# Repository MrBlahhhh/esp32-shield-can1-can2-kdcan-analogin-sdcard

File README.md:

# ESP32-S3 automotive I/O carrier — two CAN buses, K-line, microSD, analog

## TL;DR

A carrier board an **ESP32-S3-DevKitC-1 plugs into**, turning it into a
vehicle data logger. The dev board brings the MCU and its power; this board
brings everything that has to touch a car.

- **Two CAN buses at once.** One on the ESP32's own TWAI controller, one on
  an MCP2518FD over SPI — because the S3 has exactly one TWAI and two
  transceivers on it would only ever give you a choice, not both.
- **K-line (ISO 9141 / KWP2000) as well**, so a BMW/MINI K+DCAN cable is
  covered end to end. A solder jumper picks whether the aux harness pins
  carry K-line or the second CAN pair; the two cannot share a wire.
- **Four analog channels, read differentially.** The sensor loom's own
  ground comes back as a Kelvin wire through an attenuator matched to the
  signal channels', so chassis offset subtracts out exactly instead of
  landing on every reading.
- **The card survives ignition-off.** A supercapacitor bank holds the 5 V
  rail for about 825 ms after the supply goes away — six times what the board
  this forked from shipped with, and long enough to finish the block in
  flight and close the file.
- **The Python in `gen/` is the source.** It generates, places, routes,
  audits and circuit-simulates the whole board; the KiCad files are build
  outputs. `python gen/build_board.py` rebuilds the PCB from nothing.
- **The firmware runs before the board exists.** `gen/simulate_firmware.py`
  compiles the real sketch for the PC against a model of this board and
  feeds it CAN frames, sensor voltages and a power cut.
- **State: routed clean, simulated, firmware ported, never manufactured.**

## Why a carrier and not a shield

It was going to be a shield. It measured out at 1.4× the dev board's entire
area before a single track was drawn, so it isn't one — the DevKitC-1 drops
into two 22-way sockets on a board considerably larger than itself.

Worth being plain: at **98 × 100 mm** this is no smaller than the standalone
board it forked from. What it buys is a replaceable MCU with no module to
reflow, and a second CAN bus and a K-line the parent never had.

| | |
|---|---|
| Board | 98 × 100 mm, 4 layer |
| Parts | 153 component instances, 70 distinct BOM lines |
| Nets | 90 |
| Assembly | 128 surface-mount designators across 48 fab BOM lines |

## What's on it

| Block | Detail |
|---|---|
| **CAN 1** | TJA1051T/3 on the ESP32's TWAI. Common-mode choke, split termination (off by default), bidirectional clamps. |
| **CAN 2** | MCP2518FD (SOIC-14) on SPI with a 40 MHz crystal, its own TJA1051, choke, termination and clamps. |
| **K-line** | Discrete: 2N7002 low-side driver, clamped 22k/10k receiver, optional ISO 9141 tester pull-up on a jumper. |
| **Analog** | 4 channels, fixed 0–16 V divider (0.1 % where it sets the gain, 0.235 % worst case, no calibration needed), pull-up jumper per channel, two ADS1115s, shared Kelvin ground return. |
| **microSD** | 1-bit SDMMC, switched card supply, ESD arrays on every contact. |
| **Hold-up** | 2 × 0.33 F 2.7 V supercaps in series on the 5 V rail, TLV431 power-fail detector tripping at 4.20 V. |
| **Shift light** | 74AHCT1G125 buffer so WS2812 DIN is a real 5 V, fused tap, 3-pin header. |

There is **no power conversion**. Both rails come up from the dev board's
sockets — 5 V from its USB-C behind its own Schottky, 3.3 V from its LDO.
The only 12 V the board sees is OBD-II pin 16, and that is sense-only.

## Pin map

All 24 usable DevKitC-1 GPIOs are allocated; nothing is spare. Pins are
grouped by which socket row they are on, because each row is 22 through-holes
that cut a 53 mm slot through every inner layer — a signal crossing one has
no return path underneath it.

| J1 row (left of the board) | | J3 row (right) | |
|---|---|---|---|
| IO4–IO7 | AIN1–4 | IO1, IO2 | K-line RX / TX |
| IO8 | battery sense | IO39–IO42 | CAN 2 SPI (SCK/MOSI/MISO/CS) |
| IO9, IO10 | I²C SCL / SDA | IO21 | CAN 2 interrupt |
| IO11 | SD card detect | IO47 | SD supply enable |
| IO12–IO14 | SD D0 / CMD / CLK | IO48 | WS2812 data |
| IO15 | power fail | | |
| IO16–IO18 | CAN 1 S / TX / RX | | |

Exactly one net crosses sides — `SD_PWR_EN`, a load-switch gate — and it
routes around the end of the row rather than through it.

The analog channels must live in IO1–IO10 because ADC2 is unusable with the
radio up. After the SD bus takes IO9–IO14 and IO3 is excluded as a strapping
pin, IO4–IO8 are exactly the five that remain.

## Ordering

```
python gen/export_fab.py      # gerbers, positions, JLC BOM
python gen/export_order.py    # LCSC shopping list + what to buy elsewhere
```

Every one of the 48 fab BOM lines carries an LCSC part number, and each was
checked against the live catalogue rather than assumed — see
[`docs/PARTS.md`](docs/PARTS.md) for what that turned up, including three
part numbers that were confidently wrong and two footprints that would not
have soldered. [`docs/COST.md`](docs/COST.md) prices the result and identifies
about $5.70 a board of savings that cost nothing functional.

`fab/order-elsewhere.csv` lists what LCSC's assembly flow cannot supply:
the through-hole connectors, the two supercapacitors and the dev board.

**The order is ready and paused.** Everything is verified — gerbers, BOM,
placements, both JLCPCB quotes and an LCSC cart — and it is on hold because
US customs adds 35% of merchandise value. See
[`docs/TODO.md`](docs/TODO.md) for the state of play and the resume
checklist, and [`docs/COST.md`](docs/COST.md) for the quotes and the
hand-build-versus-assembled comparison.

## Verification

| | |
|---|---|
| `gen/validate.py` | schematic re-extracted through KiCad and compared net for net; ERC clean |
| `gen/build_board.py` | places, routes, and runs DRC — **0 violations, 0 unconnected** |
| `gen/simulate_firmware.py` | **50 checks**, the real sketch compiled for the host against a model of this board |
| `gen/mutate_firmware.py` | deliberately breaks the firmware 17 ways to prove the suite notices — **17 of 17 caught** |
| `gen/simulate.py` | ngspice: analog channel, crank, CAN bus, system budgets, log fidelity |
| `gen/audit_*.py` | docs, polarity, straps, paste, mechanical, PCB, routes, schematic readability |

Study 0 of the firmware suite is the one everything else rests on: it dumps
the simulator's pin map and compares it to `netlist.txt`, so a model built
from prose instead of the design fails loudly rather than validating the
wrong board.

## Wanted, not yet built

[`docs/TODO.md`](docs/TODO.md) — additions nobody has started, as opposed to
the defects below, plus the state of the paused parts order. Currently two
sensor additions, and **neither needs a board change**:

- **Exhaust gas temperature** through an MCP9600 on the I2C header. Entirely
  firmware.
- **Wideband AFR** from a DIY-EFI TinyWB. Its 0–5 V output drops straight
  into a sensor channel with nothing to change at all — that is the input
  the analogue front end was designed around. The open question is its
  10–20 AFR scaling, which clips anything richer than 10.0.

## Known open

- ~~**`ROW_PITCH` is an assumption.**~~ **Settled — 22.86 mm is correct**, from
  Espressif's own DXF. The pad columns sit at x = 1.270 and x = 24.130, 22
  pads each over y 7.960–61.300 (53.34 mm = 21 × 2.54), so the spacing is
  24.130 − 1.270 = **22.860 mm exactly**. It closes against the board width
  too: 1.270 + 22.860 + 1.270 = 25.400.

  Worth knowing that a figure of "25.4 mm row spacing on a 27.9 mm board"
  circulates for this part. That is the **original ESP32-DevKitC** with the
  WROOM-32 module, which really is wider. On the S3, 25.40 mm is the board
  width — the tell is that a 25.5 mm body with 25.4 mm rows would put the pin
  centres 0.05 mm from the edge.
- **No antenna keepout.** The module is on the dev board now, radiating from
  about 8.5 mm above this laminate. Copper underneath still detunes it, but
  which end of the outline to clear needs measuring off the same DXF.
- **The hold-up timings are calculated, not measured.** 825 ms shed /
  254 ms unshed come from `t = C·dV/I`; the ngspice study for the supercap
  bank has not been written, and ESR and the Schottky's drop over
  temperature will both eat into them.
- **Check the dev board revision.** v1.1 puts the onboard RGB LED on IO38,
  which this board leaves free for it. Some revisions use IO48, which is the
  WS2812 output here and would clash.
- **The schematic still has about 20 text collisions** out of the ~150 it
  started with, mostly a label brushing a neighbour inside a hand-drawn
  block. `gen/audit_schematic.py` lists each one with coordinates.
- **Two bypass capacitors sit 8.7 mm from the pin they bypass**, against the
  6 mm `gen/audit_pcb.py` asks for. That is the width of the SOIC-8 itself:
  the shelf packer keeps each bypass immediately beside its IC, but fills
  left to right, so the capacitor lands on the opposite side of the package
  from the supply pin. Down from 42 mm, and fine for 500 kbit/s CAN with
  22 µF of bulk on the same rail, but it is the one placement the audit
  still objects to.

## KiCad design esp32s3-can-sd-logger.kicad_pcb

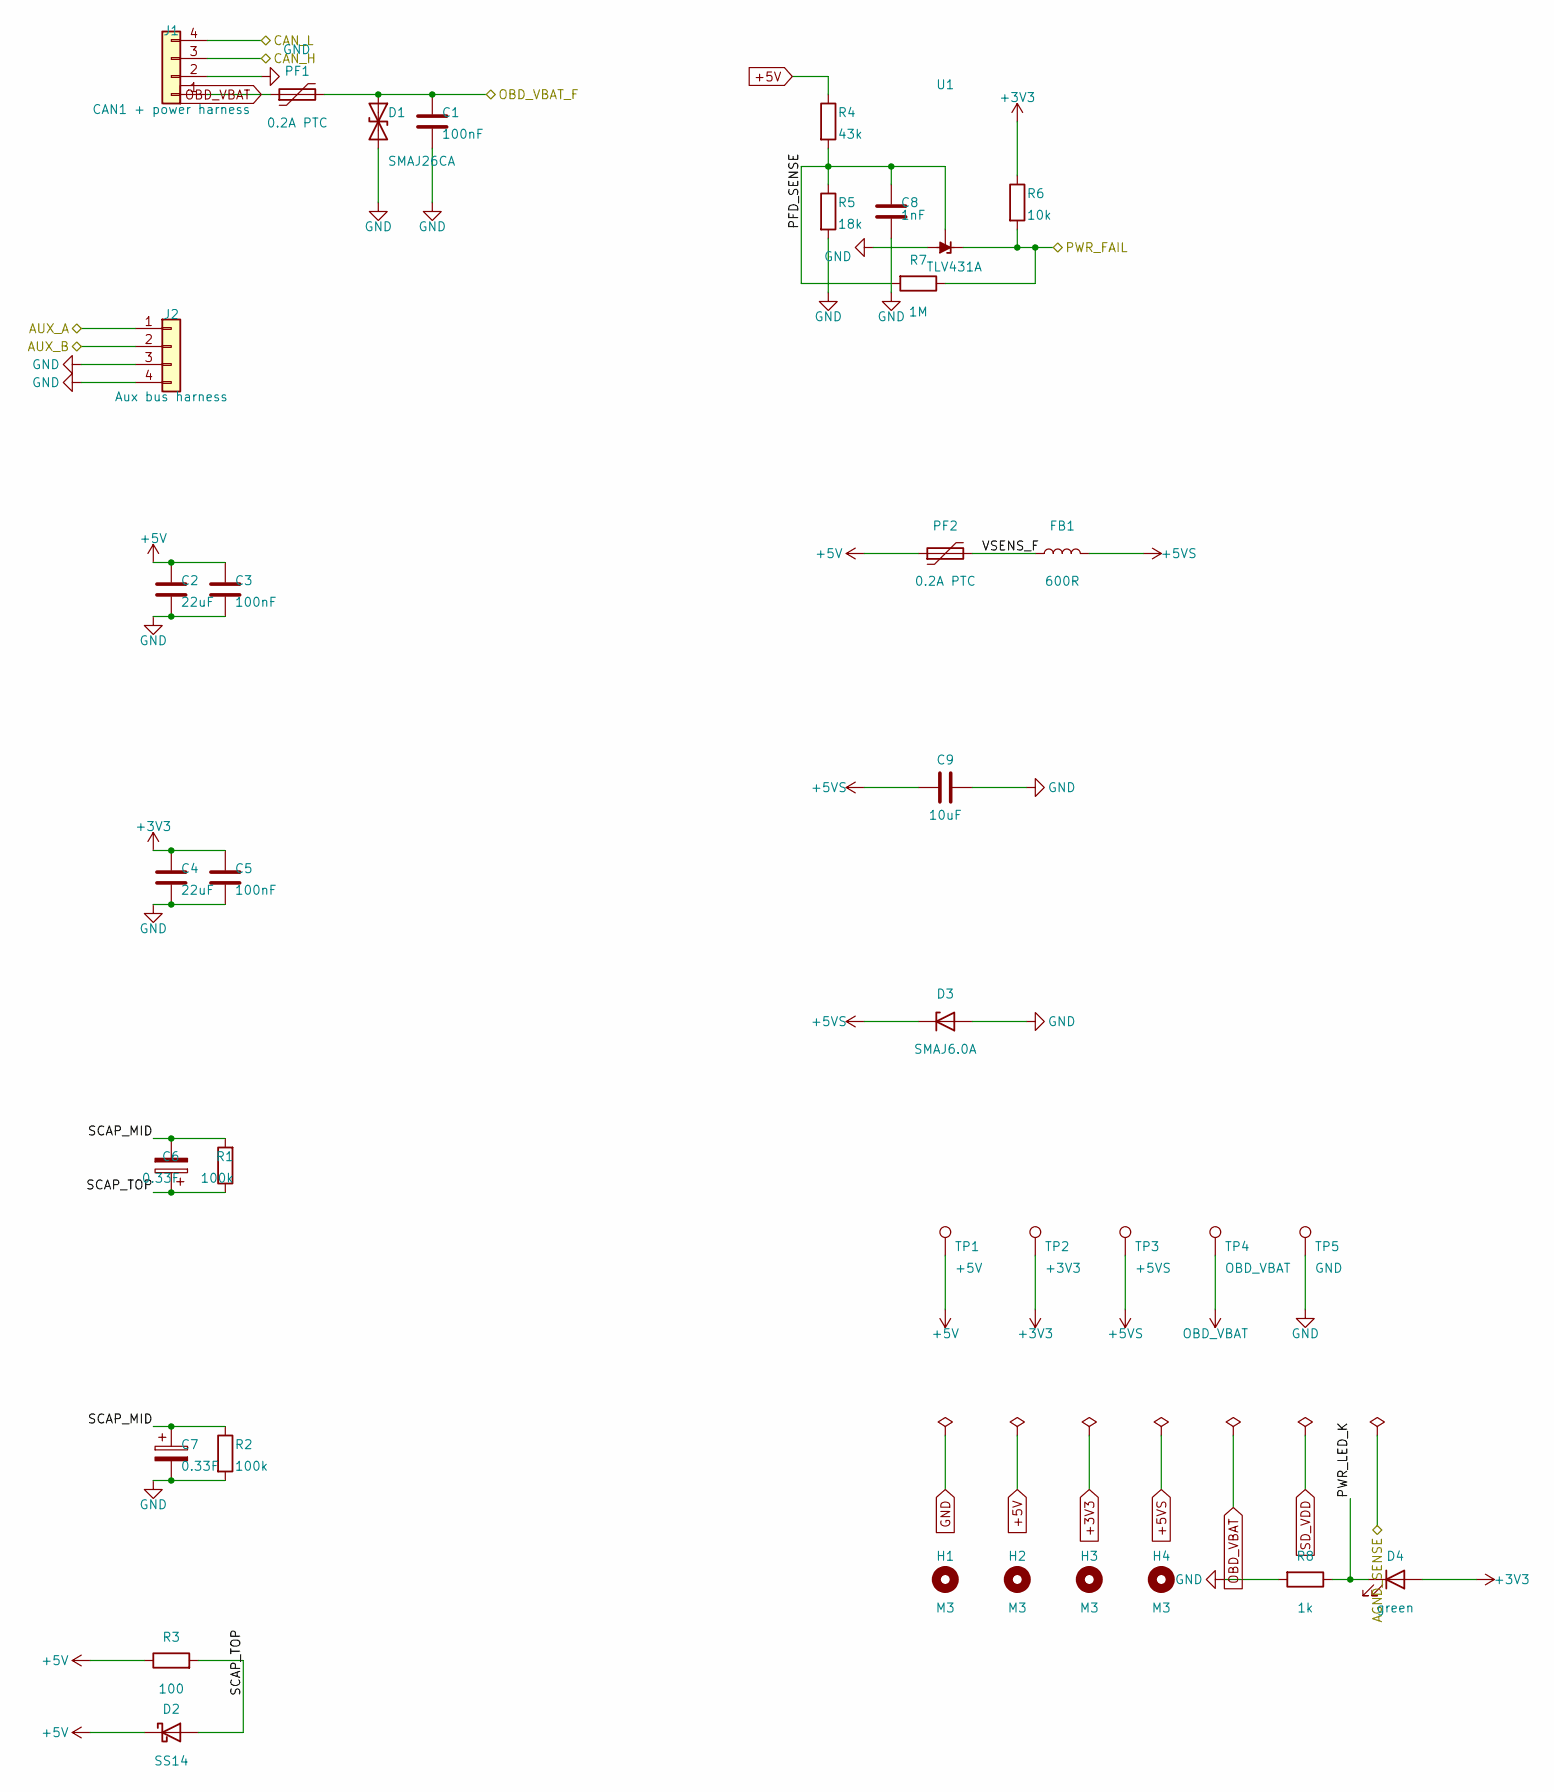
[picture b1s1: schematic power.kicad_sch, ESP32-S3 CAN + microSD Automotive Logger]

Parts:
C1: 100nF; C_0805_2012Metric; Voltage 100V
C2, C4: 22uF; C_1206_3216Metric; Voltage 16V
C3, C5: 100nF; C_0805_2012Metric; Voltage 16V
C6, C7: 0.33F; CP_Radial_D8.0mm_P3.50mm; Voltage 2.7V; MPN Eaton HB1030-2R5105-R
C8: 1nF; C_0805_2012Metric; Voltage 50V
C9: 10uF; C_1206_3216Metric; Voltage 16V
D1: SMAJ26CA; D_SMA; MPN Diodes Inc SMAJ26CA-13-F
D2: SS14; D_SMA; MPN SS14
D3: SMAJ6.0A; D_SMA; MPN Littelfuse SMAJ6.0A
D4: green; LED_0805_2012Metric
FB1: 600R; L_0805_2012Metric; MPN Wurth 742792022
H1, H2, H3, H4: M3; MountingHole_3.2mm_M3
J1: CAN1 + power harness; JST_PH_B4B-PH-K_1x04_P2.00mm_Vertical; MPN JST B4B-PH-K-S(LF)(SN)
J2: Aux bus harness; JST_PH_B4B-PH-K_1x04_P2.00mm_Vertical; MPN JST B4B-PH-K-S(LF)(SN)
PF1, PF2: 0.2A PTC; R_1812_4532Metric; MPN Bourns MF-MSMF020/60-2
R1, R2: 100k; R_0805_2012Metric
R3: 100; R_1206_3216Metric
R4: 43k; R_0805_2012Metric; Tolerance 1%
R5: 18k; R_0805_2012Metric; Tolerance 1%
R6: 10k; R_0805_2012Metric
R7: 1M; R_0805_2012Metric
R8: 1k; R_0805_2012Metric
TP1: +5V; TestPoint_Pad_D1.5mm
TP2: +3V3; TestPoint_Pad_D1.5mm
TP3: +5VS; TestPoint_Pad_D1.5mm
TP4: OBD_VBAT; TestPoint_Pad_D1.5mm
TP5: GND; TestPoint_Pad_D1.5mm
U1: TLV431A; SOT-23; MPN TLV431ASN1T1G

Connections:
+3V3: C4.1, C5.1, D4.2 (A), R6.1, TP2.1; also elsewhere on the board
+5V: C2.1, C3.1, D2.1 (K), PF2.1, R3.1, R4.1, TP1.1; also elsewhere on the board
+5VS: C9.1, D3.1 (K), FB1.2, TP3.1; also elsewhere on the board
AUX_A: J2.1; also elsewhere on the board
AUX_B: J2.2; also elsewhere on the board
CAN_H: J1.3; also elsewhere on the board
OBD_VBAT: J1.1, PF1.1, TP4.1; also elsewhere on the board
OBD_VBAT_F: C1.1, D1.1 (A1), PF1.2; also elsewhere on the board
PFD_SENSE: C8.1, R4.2, R5.1, R7.2, U1.2 (REF)
PWR_FAIL: R6.2, R7.1, U1.1 (K); also elsewhere on the board
PWR_LED_K: D4.1 (K), R8.1
SCAP_MID: C6.2, C7.1, R1.2, R2.1
SCAP_TOP: C6.1, D2.2 (A), R1.1, R3.2
VSENS_F: FB1.1, PF2.2

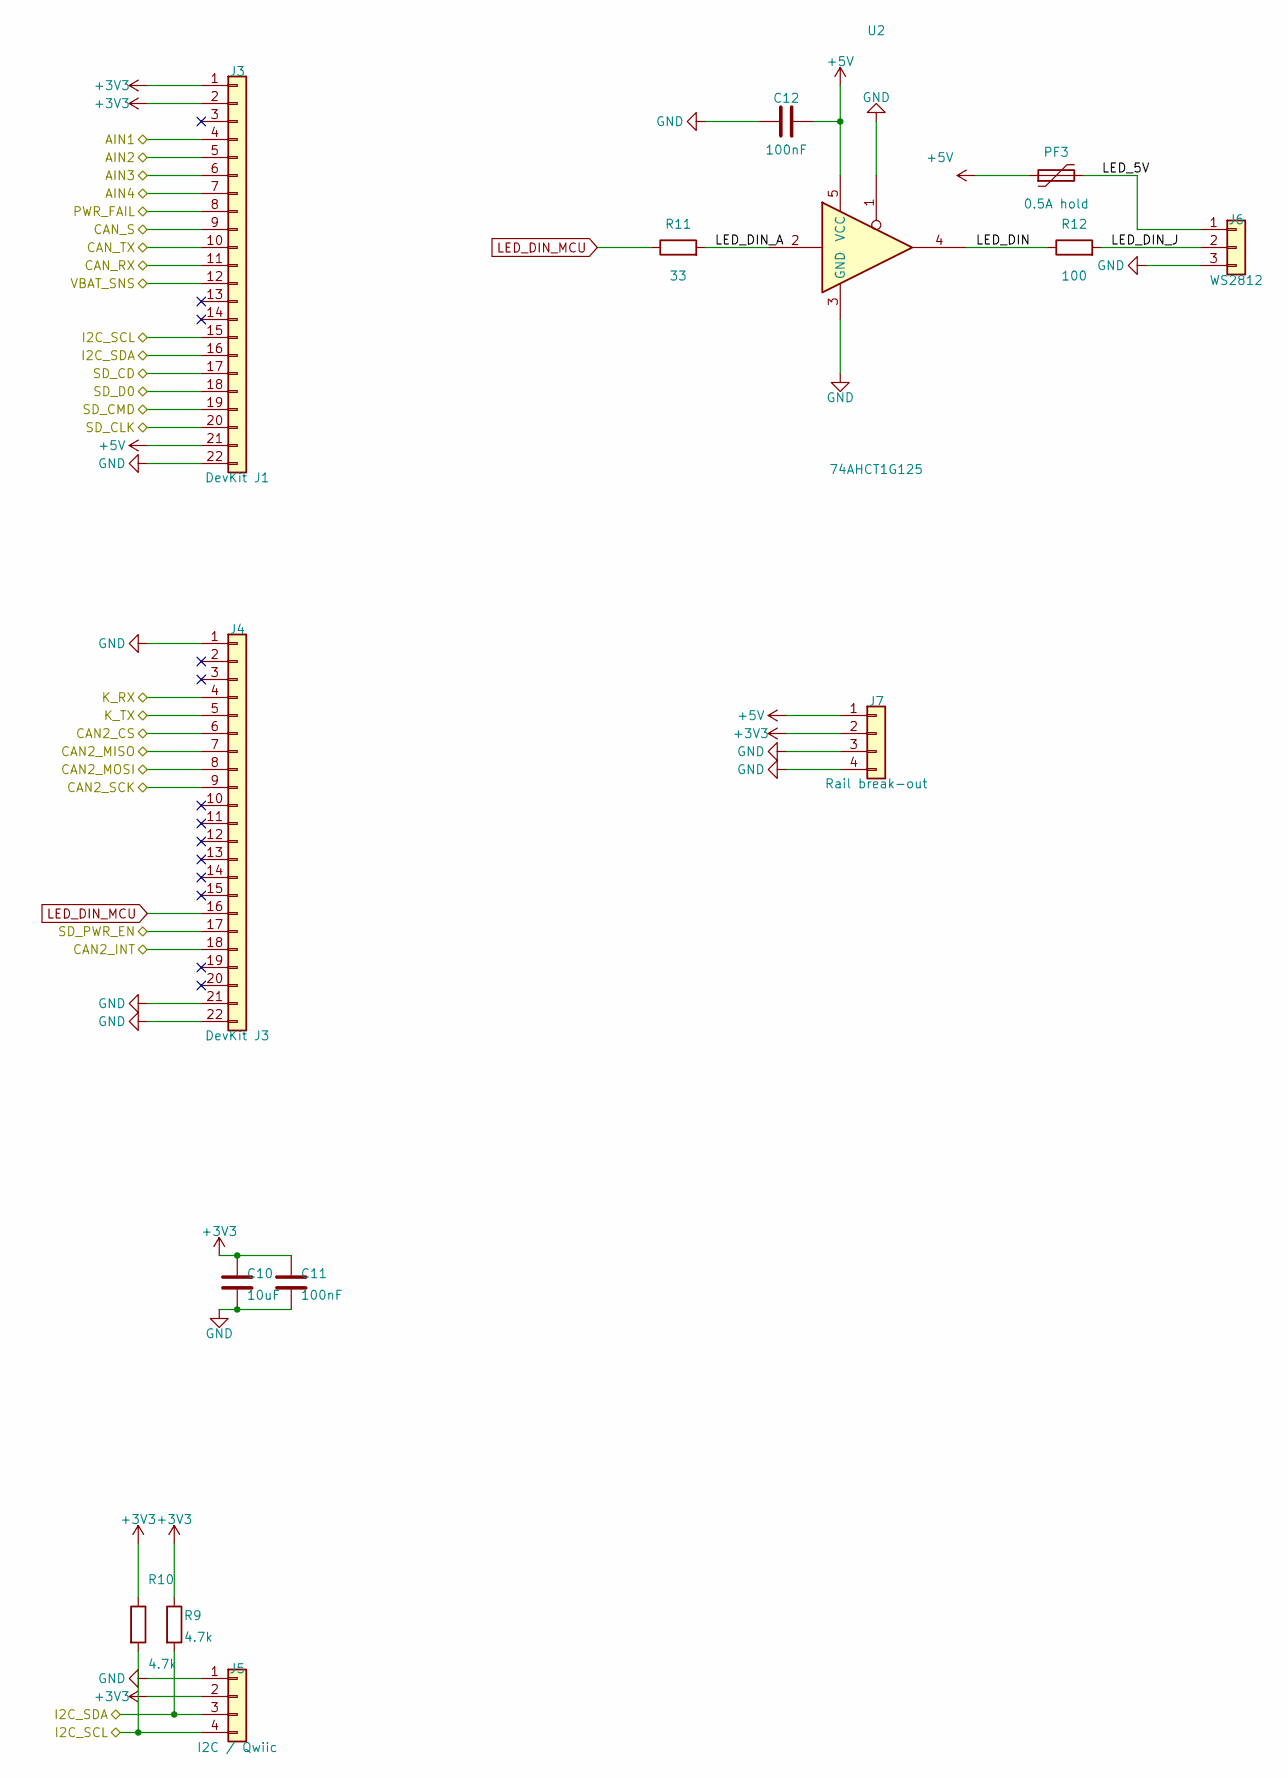
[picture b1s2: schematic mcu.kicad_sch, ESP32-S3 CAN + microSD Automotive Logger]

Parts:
C10: 10uF; C_1206_3216Metric; Voltage 16V
C11, C12: 100nF; C_0805_2012Metric; Voltage 16V
J3: DevKit J1; PinSocket_1x22_P2.54mm_Vertical; MPN ESP32-S3-DevKitC-1 J1
J4: DevKit J3; PinSocket_1x22_P2.54mm_Vertical; MPN ESP32-S3-DevKitC-1 J3
J5: I2C / Qwiic; PinHeader_1x04_P2.54mm_Vertical
J6: WS2812; PinHeader_1x03_P2.54mm_Vertical
J7: Rail break-out; PinHeader_1x04_P2.54mm_Vertical
PF3: 0.5A hold; R_1812_4532Metric; MPN Bourns MF-MSMF050-2
R9, R10: 4.7k; R_0805_2012Metric
R11: 33; R_0805_2012Metric
R12: 100; R_0805_2012Metric
U2: 74AHCT1G125; SOT-23-5; MPN SN74AHCT1G125DBVR

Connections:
+3V3: C10.1, C11.1, J3.1, J3.2, J5.2, J7.2, R9.1, R10.1; also elsewhere on the board
+5V: C12.1, J3.21, J7.1, PF3.1, U2.5 (VCC); also elsewhere on the board
AIN1: J3.4; also elsewhere on the board
AIN2: J3.5; also elsewhere on the board
AIN3: J3.6; also elsewhere on the board
AIN4: J3.7; also elsewhere on the board
CAN2_CS: J4.6; also elsewhere on the board
CAN2_INT: J4.18; also elsewhere on the board
CAN2_MISO: J4.7; also elsewhere on the board
CAN2_MOSI: J4.8; also elsewhere on the board
CAN2_SCK: J4.9; also elsewhere on the board
CAN_RX: J3.11; also elsewhere on the board
CAN_S: J3.9; also elsewhere on the board
CAN_TX: J3.10; also elsewhere on the board
I2C_SCL: J3.15, J5.4, R10.2; also elsewhere on the board
I2C_SDA: J3.16, J5.3, R9.2; also elsewhere on the board
K_RX: J4.4; also elsewhere on the board
K_TX: J4.5; also elsewhere on the board
LED_5V: J6.1, PF3.2
LED_DIN: R12.1, U2.4
LED_DIN_A: R11.2, U2.2
LED_DIN_J: J6.2, R12.2
LED_DIN_MCU: J4.16, R11.1
PWR_FAIL: J3.8; also elsewhere on the board
SD_CD: J3.17; also elsewhere on the board
SD_CLK: J3.20; also elsewhere on the board
SD_CMD: J3.19; also elsewhere on the board
SD_D0: J3.18; also elsewhere on the board
SD_PWR_EN: J4.17; also elsewhere on the board
VBAT_SNS: J3.12; also elsewhere on the board

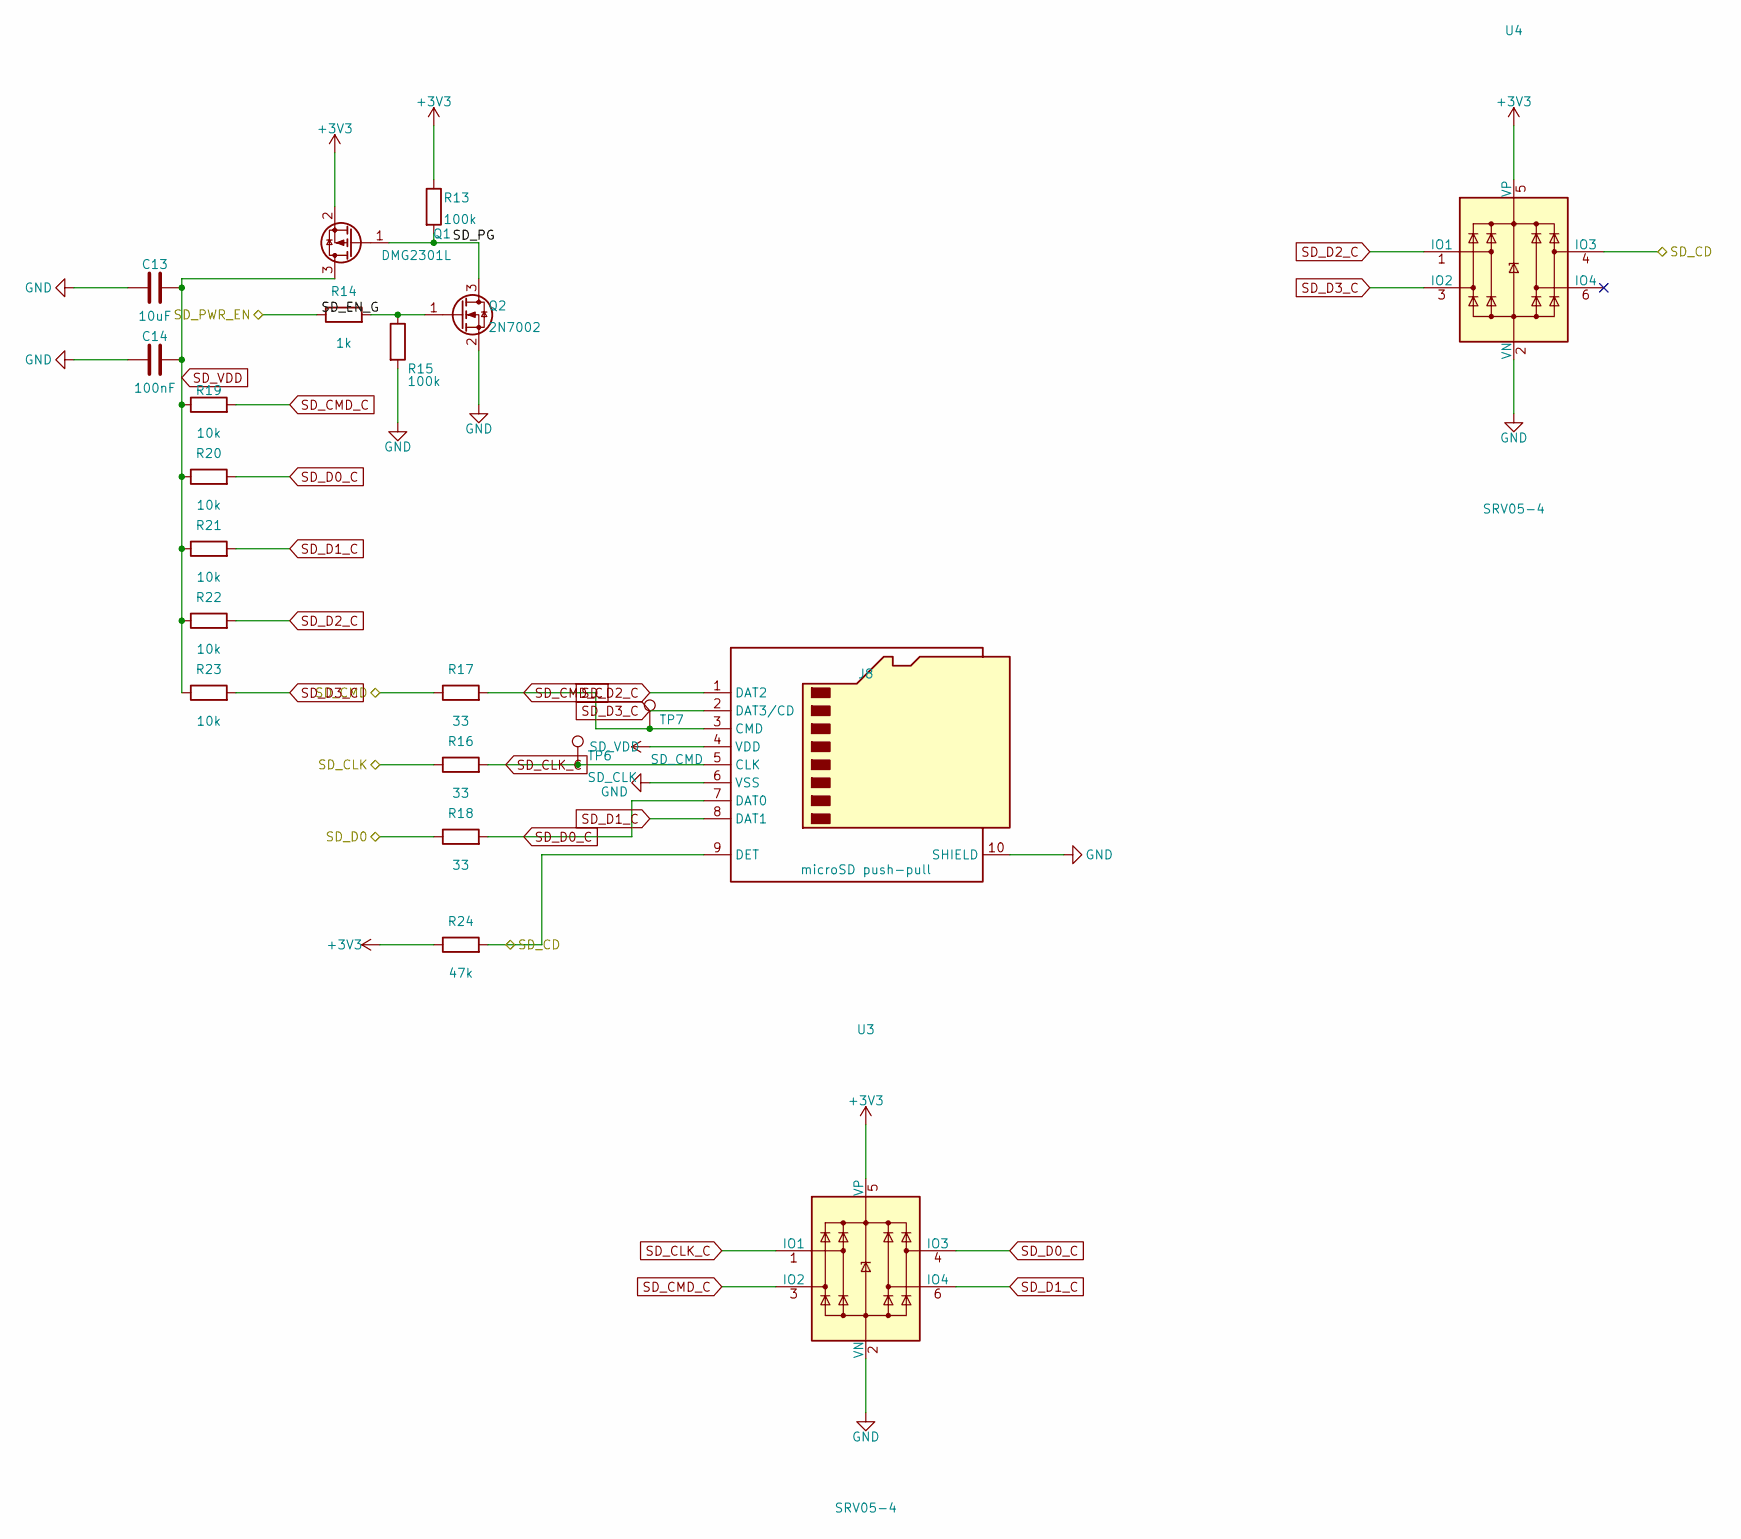
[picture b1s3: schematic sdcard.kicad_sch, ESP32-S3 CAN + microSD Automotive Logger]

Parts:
C13: 10uF; C_1206_3216Metric; Voltage 16V
C14: 100nF; C_0805_2012Metric; Voltage 16V
J8: microSD push-pull; microSD_HC_Hirose_DM3D-SF; MPN Hirose DM3D-SF
Q1: DMG2301L; SOT-23; MPN DMG2301L
Q2: 2N7002; SOT-23; MPN 2N7002
R13, R15: 100k; R_0805_2012Metric
R14: 1k; R_0805_2012Metric
R16, R17, R18: 33; R_0805_2012Metric
R19, R20, R21, R22, R23: 10k; R_0805_2012Metric
R24: 47k; R_0805_2012Metric
TP6: SD_CLK; TestPoint_Pad_D1.5mm
TP7: SD_CMD; TestPoint_Pad_D1.5mm
U3, U4: SRV05-4; SOT-23-6; MPN Semtech SRV05-4.TCT

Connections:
+3V3: Q1.2 (S), R13.1, R24.1, U3.5 (VP), U4.5 (VP); also elsewhere on the board
SD_CD: J8.9 (DET), R24.2, U4.4 (IO3); also elsewhere on the board
SD_CLK: R16.1; also elsewhere on the board
SD_CLK_C: J8.5 (CLK), R16.2, TP6.1, U3.1 (IO1)
SD_CMD: R17.1; also elsewhere on the board
SD_CMD_C: J8.3 (CMD), R17.2, R19.2, TP7.1, U3.3 (IO2)
SD_D0: R18.1; also elsewhere on the board
SD_D0_C: J8.7 (DAT0), R18.2, R20.2, U3.4 (IO3)
SD_D1_C: J8.8 (DAT1), R21.2, U3.6 (IO4)
SD_D2_C: J8.1 (DAT2), R22.2, U4.1 (IO1)
SD_D3_C: J8.2 (DAT3/CD), R23.2, U4.3 (IO2)
SD_EN_G: Q2.1 (G), R14.2, R15.1
SD_PG: Q1.1 (G), Q2.3 (D), R13.2
SD_PWR_EN: R14.1; also elsewhere on the board
SD_VDD: C13.1, C14.1, J8.4 (VDD), Q1.3 (D), R19.1, R20.1, R21.1, R22.1, R23.1

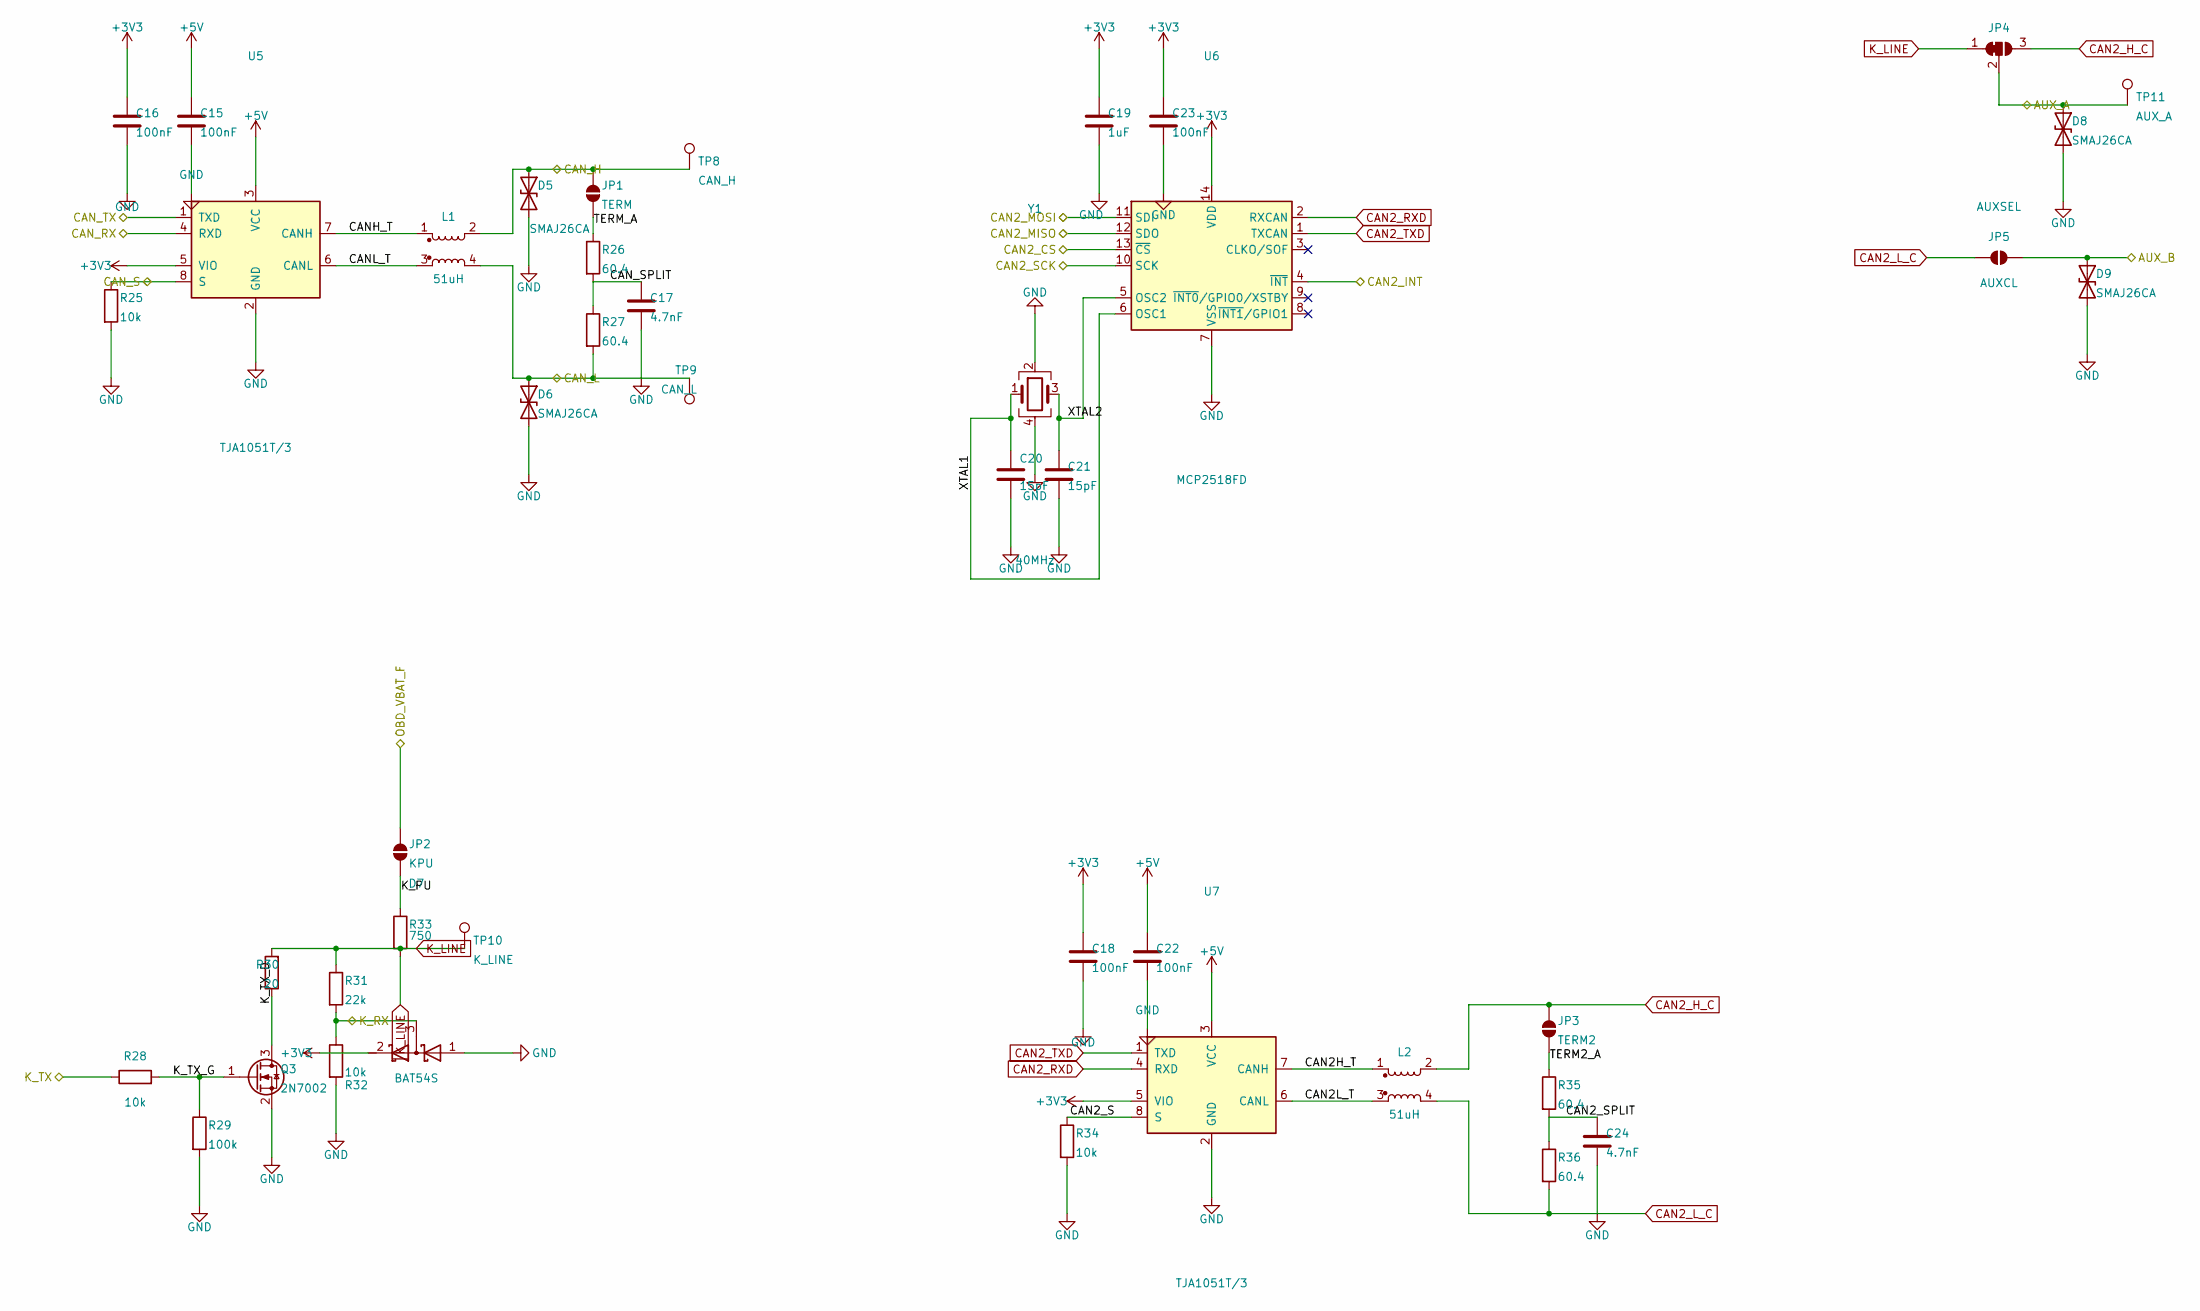
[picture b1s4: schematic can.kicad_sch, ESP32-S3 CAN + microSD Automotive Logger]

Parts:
C15, C16, C18, C22, C23: 100nF; C_0805_2012Metric; Voltage 16V
C17, C24: 4.7nF; C_0805_2012Metric; Voltage 50V
C19: 1uF; C_0805_2012Metric; Voltage 16V
C20, C21: 15pF; C_0805_2012Metric; Voltage 50V
D5, D6, D8, D9: SMAJ26CA; D_SMA; MPN Diodes Inc SMAJ26CA-13-F
D7: BAT54S; SOT-23; MPN MDD BAT54S
JP1: TERM; SolderJumper-2_P1.3mm_Open_Pad1.0x1.5mm
JP2: KPU; SolderJumper-2_P1.3mm_Open_Pad1.0x1.5mm
JP3: TERM2; SolderJumper-2_P1.3mm_Open_Pad1.0x1.5mm
JP4: AUXSEL; SolderJumper-3_P1.3mm_Bridged12_Pad1.0x1.5mm
JP5: AUXCL; SolderJumper-2_P1.3mm_Open_Pad1.0x1.5mm
L1, L2: 51uH; L_CommonMode_TDK_ACT45B; MPN TDK ACT45B-510-2P-TL003
Q3: 2N7002; SOT-23; MPN onsemi 2N7002
R25, R28, R32, R34: 10k; R_0805_2012Metric
R26, R27, R35, R36: 60.4; R_0805_2012Metric
R29: 100k; R_0805_2012Metric
R30: 20; R_1206_3216Metric
R31: 22k; R_0805_2012Metric
R33: 750; R_1206_3216Metric
TP8: CAN_H; TestPoint_Pad_D1.5mm
TP9: CAN_L; TestPoint_Pad_D1.5mm
TP10: K_LINE; TestPoint_Pad_D1.5mm
TP11: AUX_A; TestPoint_Pad_D1.5mm
U5, U7: TJA1051T/3; SOIC-8_3.9x4.9mm_P1.27mm; MPN TJA1051T/3,118
U6: MCP2518FD; SOIC-14_3.9x8.7mm_P1.27mm; MPN MCP2518FDT-H/SL
Y1: 40MHz; Crystal_SMD_3225-4Pin_3.2x2.5mm; MPN TX322540M4FBCE2T

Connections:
+3V3: C16.1, C18.1, C19.1, C23.1, D7.2 (K), U5.5 (VIO), U6.14 (VDD), U7.5 (VIO); also elsewhere on the board
+5V: C15.1, C22.1, U5.3 (VCC), U7.3 (VCC); also elsewhere on the board
AUX_A: D8.1 (A1), JP4.2 (C), TP11.1; also elsewhere on the board
AUX_B: D9.1 (A1), JP5.1 (A); also elsewhere on the board
CAN2H_T: L2.1, U7.7 (CANH)
CAN2L_T: L2.3, U7.6 (CANL)
CAN2_CS: U6.13 (~CS); also elsewhere on the board
CAN2_H_C: JP3.1 (A), JP4.3 (B), L2.2
CAN2_INT: U6.4 (~INT); also elsewhere on the board
CAN2_MISO: U6.12 (SDO); also elsewhere on the board
CAN2_MOSI: U6.11 (SDI); also elsewhere on the board
CAN2_RXD: U6.2 (RXCAN), U7.4 (RXD)
CAN2_S: R34.1, U7.8 (S)
CAN2_SCK: U6.10 (SCK); also elsewhere on the board
CAN2_SPLIT: C24.1, R35.2, R36.1
CAN2_TXD: U6.1 (TXCAN), U7.1 (TXD)
CANH_T: L1.1, U5.7 (CANH)
CANL_T: L1.3, U5.6 (CANL)
CAN_H: D5.1 (A1), JP1.1 (A), L1.2, TP8.1; also elsewhere on the board
CAN_RX: U5.4 (RXD); also elsewhere on the board
CAN_S: R25.1, U5.8 (S); also elsewhere on the board
CAN_SPLIT: C17.1, R26.2, R27.1
CAN_TX: U5.1 (TXD); also elsewhere on the board
K_LINE: JP4.1 (A), R30.2, R31.1, R33.2, TP10.1
K_PU: JP2.2 (B), R33.1
K_RX: D7.3 (common), R31.2, R32.1; also elsewhere on the board
K_TX: R28.1; also elsewhere on the board
K_TX_D: Q3.3 (D), R30.1
K_TX_G: Q3.1 (G), R28.2, R29.1
OBD_VBAT_F: JP2.1 (A); also elsewhere on the board
TERM2_A: JP3.2 (B), R35.1
TERM_A: JP1.2 (B), R26.1
XTAL1: C20.1, U6.6 (OSC1), Y1.1
XTAL2: C21.1, U6.5 (OSC2), Y1.3

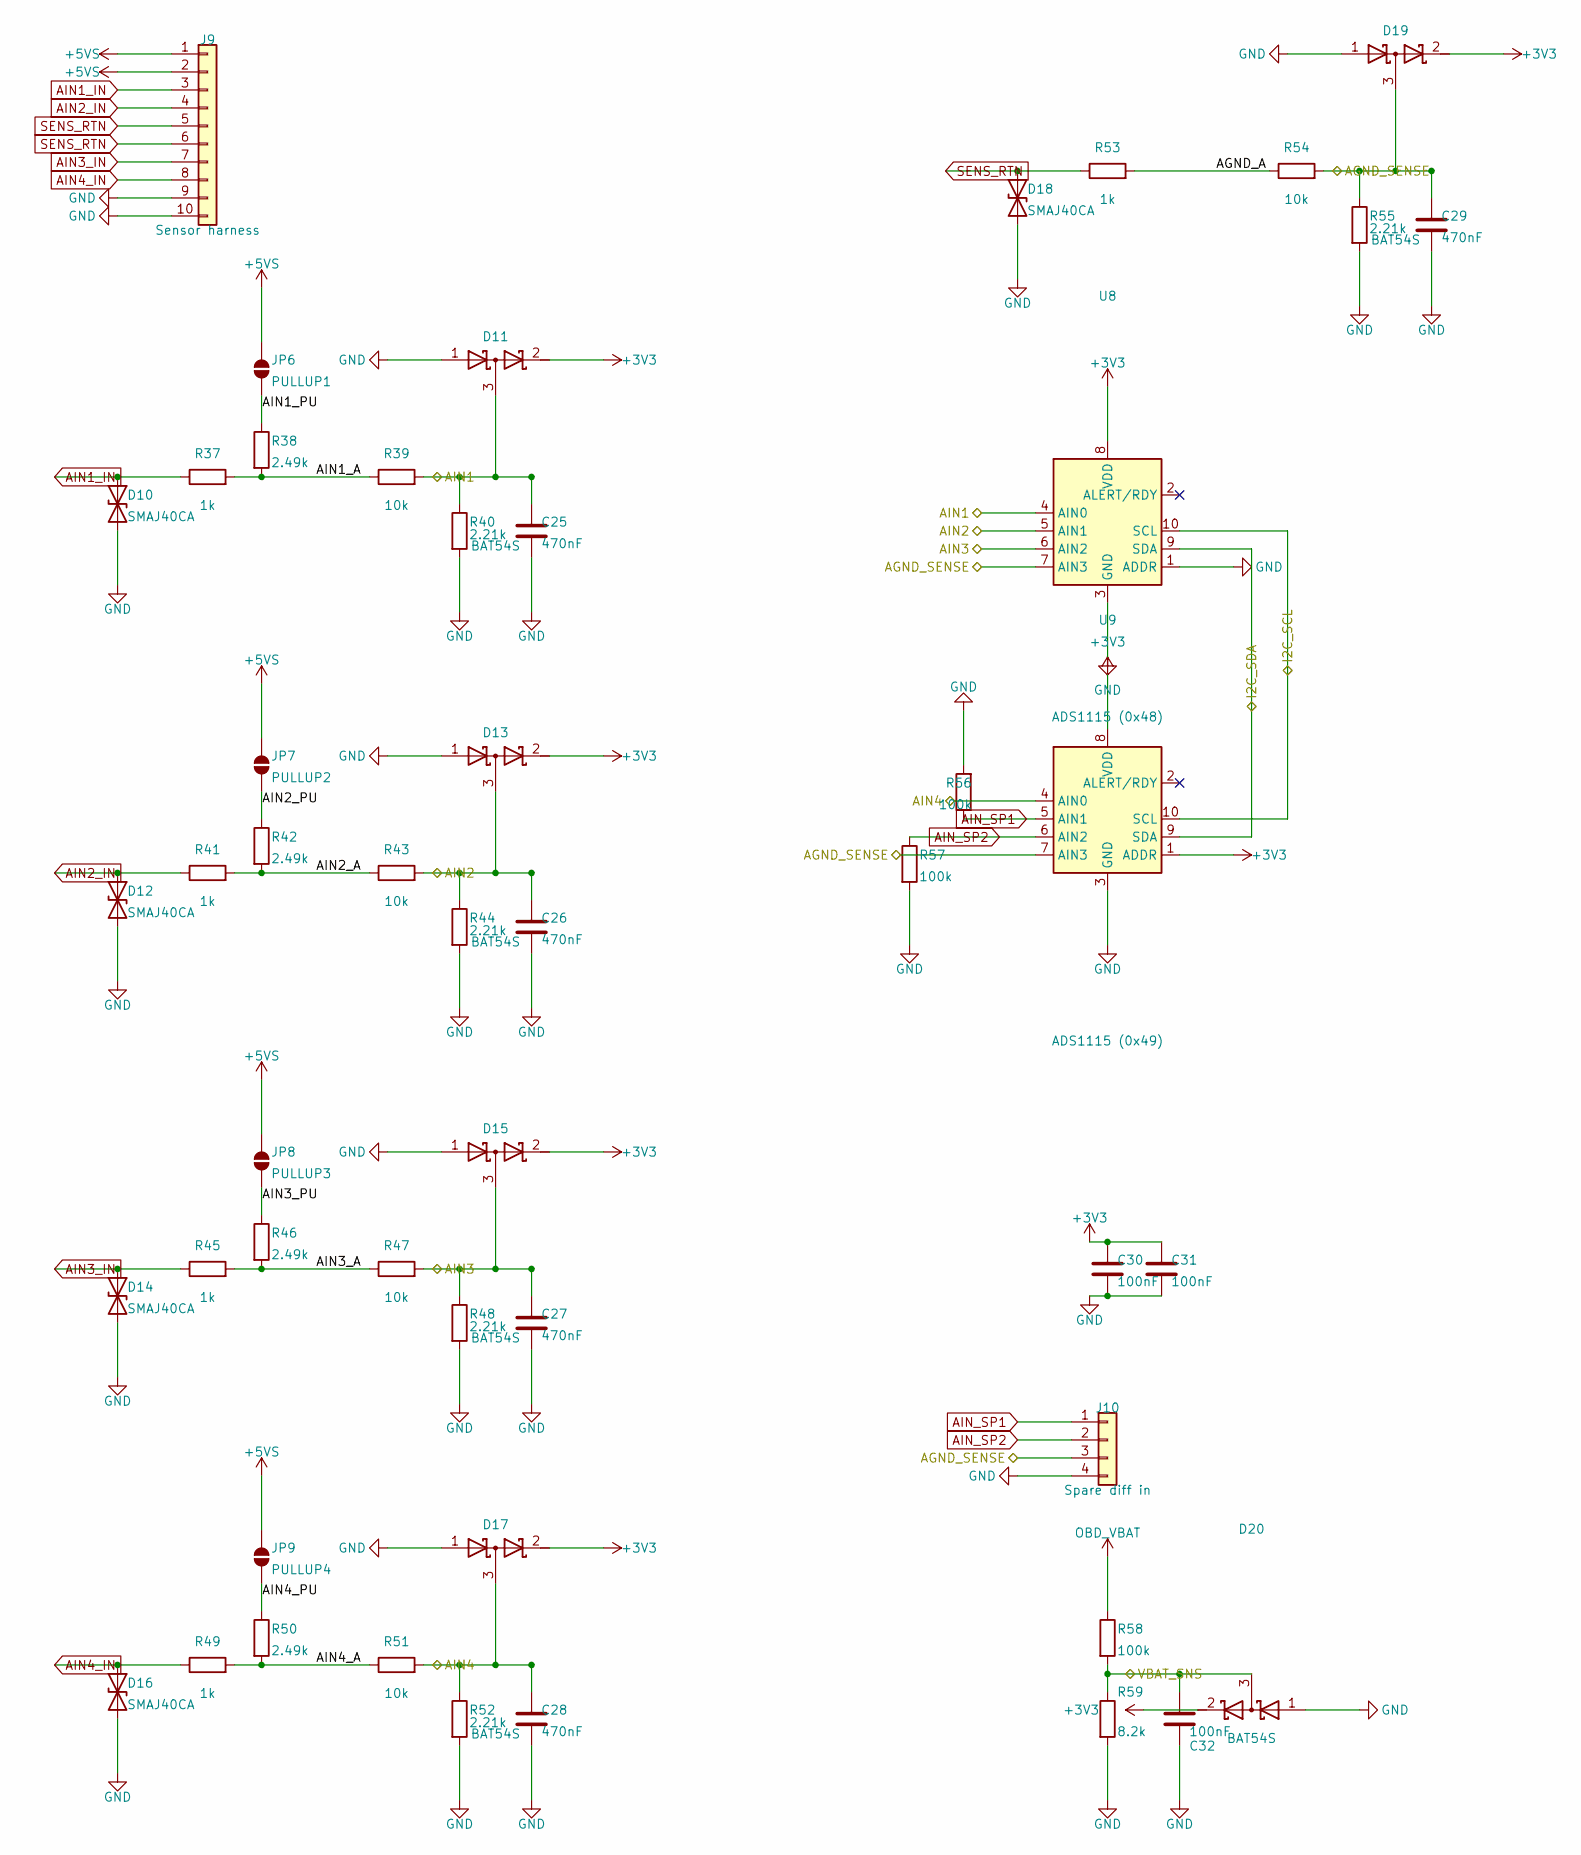
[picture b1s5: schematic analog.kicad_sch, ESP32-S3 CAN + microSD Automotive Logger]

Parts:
C25, C26, C27, C28, C29: 470nF; C_0805_2012Metric; Voltage 50V
C30, C31, C32: 100nF; C_0805_2012Metric; Voltage 16V
D10, D12, D14, D16, D18: SMAJ40CA; D_SMA; MPN Littelfuse SMAJ40CA
D11, D13, D15, D17, D19, D20: BAT54S; SOT-23; MPN MDD BAT54S
J9: Sensor harness; JST_PH_B10B-PH-K_1x10_P2.00mm_Vertical; MPN JST B10B-PH-K-S(LF)(SN)
J10: Spare diff in; PinHeader_1x04_P2.54mm_Vertical
JP6: PULLUP1; SolderJumper-2_P1.3mm_Open_Pad1.0x1.5mm
JP7: PULLUP2; SolderJumper-2_P1.3mm_Open_Pad1.0x1.5mm
JP8: PULLUP3; SolderJumper-2_P1.3mm_Open_Pad1.0x1.5mm
JP9: PULLUP4; SolderJumper-2_P1.3mm_Open_Pad1.0x1.5mm
R37, R41, R45, R49, R53: 1k; R_0805_2012Metric
R38, R42, R46, R50: 2.49k; R_0805_2012Metric
R39, R43, R47, R51, R54: 10k; R_0805_2012Metric; Tolerance 0.1%
R40, R44, R48, R52, R55: 2.21k; R_0805_2012Metric; Tolerance 0.1%
R56, R57, R58: 100k; R_0805_2012Metric
R59: 8.2k; R_0805_2012Metric
U8: ADS1115 (0x48); VSSOP-10_3x3mm_P0.5mm; MPN ADS1115IDGSR
U9: ADS1115 (0x49); VSSOP-10_3x3mm_P0.5mm; MPN ADS1115IDGSR

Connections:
+3V3: C30.1, C31.1, D11.2 (K), D13.2 (K), D15.2 (K), D17.2 (K), D19.2 (K), D20.2 (K), U8.8 (VDD), U9.1 (ADDR), U9.8 (VDD); also elsewhere on the board
+5VS: J9.1, J9.2, JP6.1 (A), JP7.1 (A), JP8.1 (A), JP9.1 (A); also elsewhere on the board
AGND_A: R53.2, R54.1
AGND_SENSE: C29.1, D19.3 (common), J10.3, R54.2, R55.1, U8.7 (AIN3), U9.7 (AIN3)
AIN1: C25.1, D11.3 (common), R39.2, R40.1, U8.4 (AIN0); also elsewhere on the board
AIN1_A: R37.2, R38.2, R39.1
AIN1_IN: D10.1 (A1), J9.3, R37.1
AIN1_PU: JP6.2 (B), R38.1
AIN2: C26.1, D13.3 (common), R43.2, R44.1, U8.5 (AIN1); also elsewhere on the board
AIN2_A: R41.2, R42.2, R43.1
AIN2_IN: D12.1 (A1), J9.4, R41.1
AIN2_PU: JP7.2 (B), R42.1
AIN3: C27.1, D15.3 (common), R47.2, R48.1, U8.6 (AIN2); also elsewhere on the board
AIN3_A: R45.2, R46.2, R47.1
AIN3_IN: D14.1 (A1), J9.7, R45.1
AIN3_PU: JP8.2 (B), R46.1
AIN4: C28.1, D17.3 (common), R51.2, R52.1, U9.4 (AIN0); also elsewhere on the board
AIN4_A: R49.2, R50.2, R51.1
AIN4_IN: D16.1 (A1), J9.8, R49.1
AIN4_PU: JP9.2 (B), R50.1
AIN_SP1: J10.1, R56.1, U9.5 (AIN1)
AIN_SP2: J10.2, R57.1, U9.6 (AIN2)
I2C_SCL: U8.10 (SCL), U9.10 (SCL); also elsewhere on the board
I2C_SDA: U8.9 (SDA), U9.9 (SDA); also elsewhere on the board
OBD_VBAT: R58.1; also elsewhere on the board
SENS_RTN: D18.1 (A1), J9.5, J9.6, R53.1
VBAT_SNS: C32.1, D20.3 (common), R58.2, R59.1; also elsewhere on the board

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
